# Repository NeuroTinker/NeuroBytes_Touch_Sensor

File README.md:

# NeuroBytes Touch Sensory Neuron

The NeuroBytes Touch Sensory Neuron is an open-source hardware neuron simulator designed and sold by [NeuroTinker, LLC](http://www.neurotinker.com/). 

All NeuroBytes products are based on the ST32L0x series of ARM Cortex-M0+ 32-bit microcontrollers. The boards were designed in KiCad and Inkscape and are released under the terms of the Creative Commons Attribution-ShareAlike 4.0 license, available here: http://creativecommons.org/licenses/by-sa/4.0/. The NeuroBytes Touch Sensory Neuron is Certified Open Source Hardware as defined by [OSHWA](https://www.oshwa.org), certification number US000110.

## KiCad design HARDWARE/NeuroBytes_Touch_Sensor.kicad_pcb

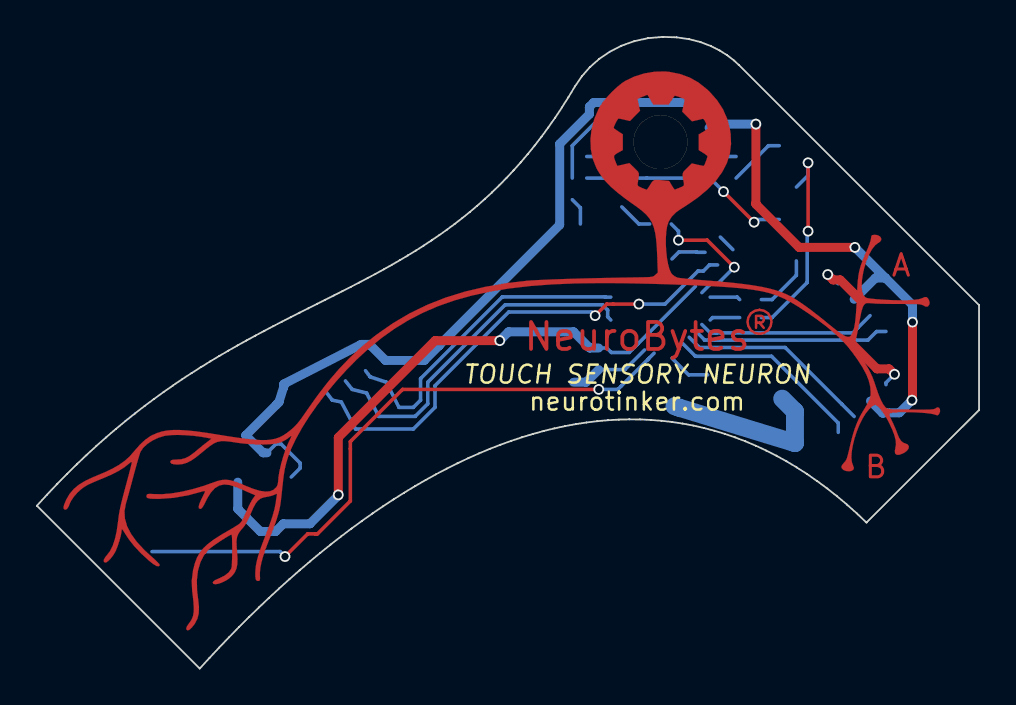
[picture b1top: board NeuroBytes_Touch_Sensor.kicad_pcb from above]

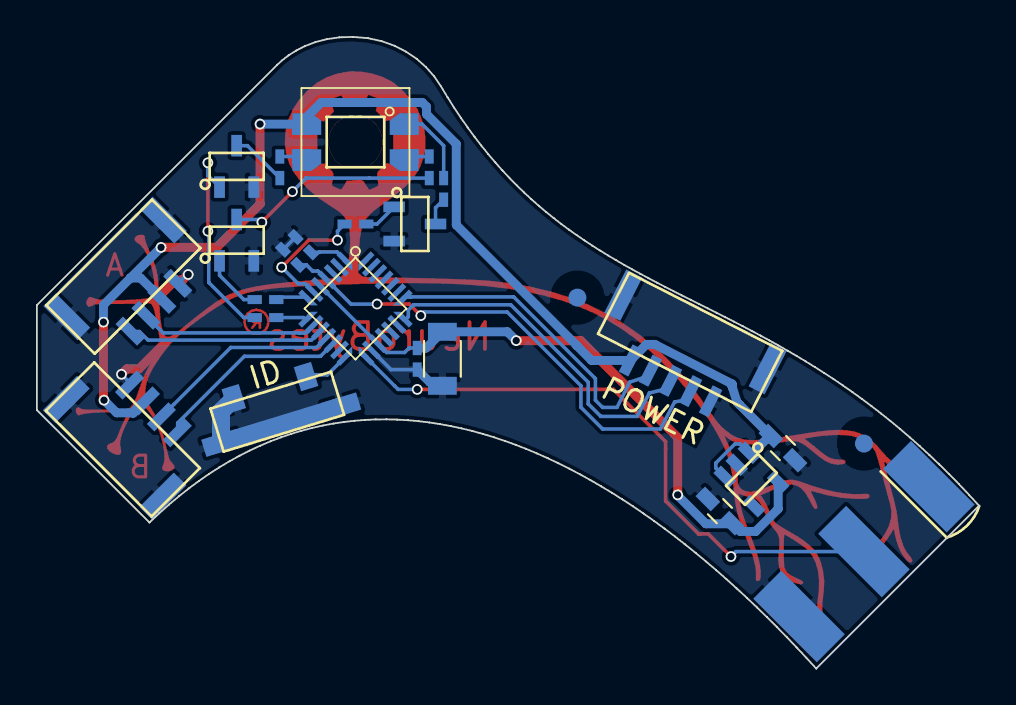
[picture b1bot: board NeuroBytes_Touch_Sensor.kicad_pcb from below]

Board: 2 copper layers, 52.3 x 35.1 mm, 23 parts (23 on the bottom side), 25 nets.

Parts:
C1, C4: 1u; C_0603_HandSoldering
C2: 10u; C_1206
C3, C5: 0u1; ZF_SMD_NonPol_0402_cap
D1: LED_RABG; ZF_LED_RGB_SunLED_XZMDKCBDDG45S-9_cast
P1: JST_GH_5-pos; ZF_CONN_JST_GH_5POS
P6, P7: CONN_01X04; ZF_CONN_JST_GH
Q1, Q2, Q3: MMBT3904; ZF_SOT23-3L
R1: 150; ZF_SMD_NonPol_0402
R2, R3: 100; ZF_SMD_NonPol_0402
R4: JMP; ZF_SMD_NonPol_0402
R5, R6, R7: 1k; ZF_SMD_NonPol_0402
SW1: SW_PUSH; ZF_SW_Momentary_SideMtg
SW2: SW_SNAP_ACTION; ZF_SW_Momentary_Snap-Action_side-mtg
U1: STM32L011Gx; ZF_IC_UFQFPN28-050
U2: 3v3 LDO; ZF_SOT23-5L

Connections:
+3V3: C2.1, C3.1, C4.1, U1.5, U1.17, U2.5
+5V: C1.1, D1.2, P1.5, P6.2, P7.2, U2.1, U2.3
A1EX: P6.4, U1.10
A1IN: P6.3, U1.9
A2EX: P7.4, U1.12
A2IN: P7.3, U1.11
GND: C1.2, C2.2, C3.2, C4.2, C5.2, P1.1, P6.1, P7.1, Q1.2, Q2.2, Q3.2, R4.1, SW1.1, SW2.1, U1.16, U2.2
IDENTIFY: SW1.2, U1.14
INPUT: SW2.2, U1.15
LED_B: R7.2, U1.8
LED_G: R6.2, U1.7
LED_R: R5.2, U1.6
unnamed: D1.1, R1.1
unnamed: D1.3, R3.1
unnamed: D1.4, R2.1
unnamed: Q1.1, R5.1
unnamed: Q1.3, R1.2
unnamed: Q2.1, R6.1
unnamed: Q2.3, R2.2
unnamed: Q3.1, R7.1
unnamed: Q3.3, R3.2
unnamed: R4.2, U1.1
RESET: C5.1, P1.2, U1.4
SWCLK: P1.4, U1.22
SWDIO: P1.3, U1.21

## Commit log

2017-04-24 Initial commit -- first rev HW and test FW.
2017-05-15 added schematic library submodule
2017-05-15 first firmware commit
2017-05-15 Board rev2. Simplified PCB outline and modified axon graphics a bit.
2017-05-15 updated firmware for new board revision
2017-05-16 Updated PCB footprints to proper rotations. Added fab documentation to PCB file. Generated Gerber files, drill file, and placement file. Generated and filled in BOM. Added switch graphic to PCB dwgs 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
2017-05-17 Minor Gerber file updates. Removed paste from SW2 (snap-action) footprint.
2017-05-18 Added front and back pictures of Rev. B PCBs. Minor photo touch-ups to clean table (mostly junk on the lens) and adjust levels.
2017-05-18 messed with levels a bit more for front img. need to improve lighting for photos.
2017-05-26 Updated libopencm3 submodule to point to NT version
2017-06-02 Updated switch and connector footprints. Changed out dual transistors and resistor network for discrete components. Other minor updates.
2017-06-29 chenged comms
2017-07-04 cleaned up
2017-08-11 Switched to 5-pin power/programming connector. Added POWER text and increased ID text size. Changed to TOUCH SENSORY NEURON. Added dendrite ID letters.
2017-08-11 added fingerprint
2017-08-11 added elf
2017-08-11 test
2017-08-11 fingerprint address
2017-08-11 update fingerprint
2017-08-11 fingerprint
2017-08-28 added kicad fonts to *.svg. added *.png render of pcb front.
2017-09-06 illustration updates
2017-09-06 illustration updates and front/back png exports
2017-09-07 added image to readme.md
2017-09-11 added downstream axon delay
2017-09-11 fixed simultaneous excitation issue
2017-09-11 made elf
2017-09-21 added *.d to .gitignore
2017-09-22 deleted extraneous files
2017-09-22 enforced .gitignore
2017-09-22 deleted old Gerber files. fresh board front export.
2017-09-22 update schematic lib
2017-09-22 updated gear shape to new design on PCB and *.svg. pulled mask back on labels. updated schematic part descriptions. fresh BOM export. other minor updates.
2017-09-22 reloaded netlist. minor PCB updates.
2017-09-27 updated to minimally modified Interneuron firmware to maintain consistency across boards (new membrane potential range, LED color scheme, comments, variable locations, etc). added adaptation mode.
2017-10-03 minor page layout updates
2017-11-01 updating to newprotocol
2017-11-01 ks demo build
2018-01-09 protocol updates
2018-01-30 resolved merge conflicts
2018-02-13 added ESD protection. minor routing changes. updated title block.
2018-03-06 added ESD protection. updated graphics.
2018-03-08 updated PCB renders (no myelination, etc). updated license/readme.
2018-03-08 saved *.svg file...
2018-03-08 added OSHWA cert logo to README.md
2018-04-10 made elf.
2018-05-23 generated fab and BOM files
2018-05-31 added schematic *.pdf export
2018-06-01 added .bin
2018-06-01 testing flashing
2018-06-01 testing flashing again
2018-06-06 regular brightness for test
2018-06-18 updated comms
2018-06-19 fixed comms bugs
2018-06-19 wokring with NID!
2018-06-19 fixed comms slowing bug
2018-08-06 added placement diagram for PCBA
2018-08-06 updated 0603 and 1206 footprints. minor routing fix. added placement pdf.
2018-08-06 re-generated Gerber files
2018-08-08 regen drill file
2018-08-08 deleted duplicate drill file
2018-12-29 increased AP brightness
2018-12-31 removed adaptation
2019-01-05 fixed #*$&ing regulator rotation that caused delays and resulted in much scrap

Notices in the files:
HARDWARE/NeuroBytes_Touch_Sensor.kicad_pcb:
(C) 2017 Zach Fredin
License: CC-BY-SA 4.0
README.md:
CC BY-SA 4.0
